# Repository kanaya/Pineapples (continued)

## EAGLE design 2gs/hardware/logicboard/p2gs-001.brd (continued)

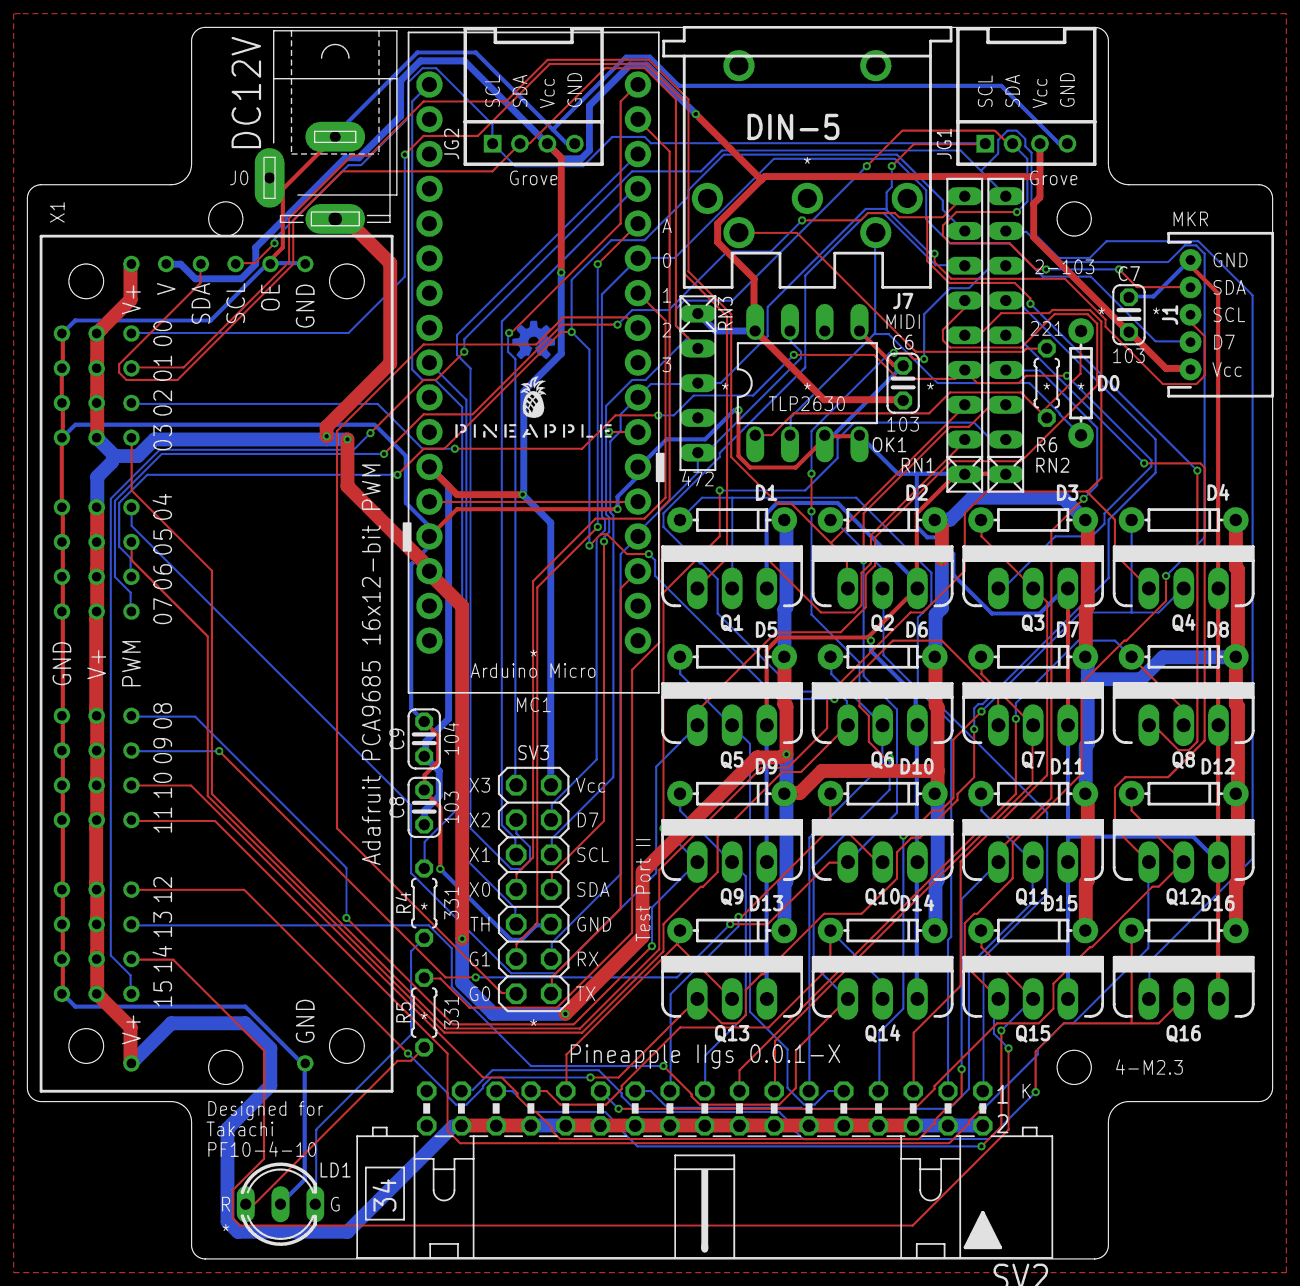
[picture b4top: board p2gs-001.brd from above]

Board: 2 copper layers, 91.0 x 90.0 mm, 56 parts (1 on the bottom side), 55 nets.

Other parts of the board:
JG2: Grove/2; 4P-2.0-90D

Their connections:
GND: JG2.4; also elsewhere on the board
SCL: JG2.1; also elsewhere on the board
SDA: JG2.2; also elsewhere on the board
VCC: JG2.3; also elsewhere on the board

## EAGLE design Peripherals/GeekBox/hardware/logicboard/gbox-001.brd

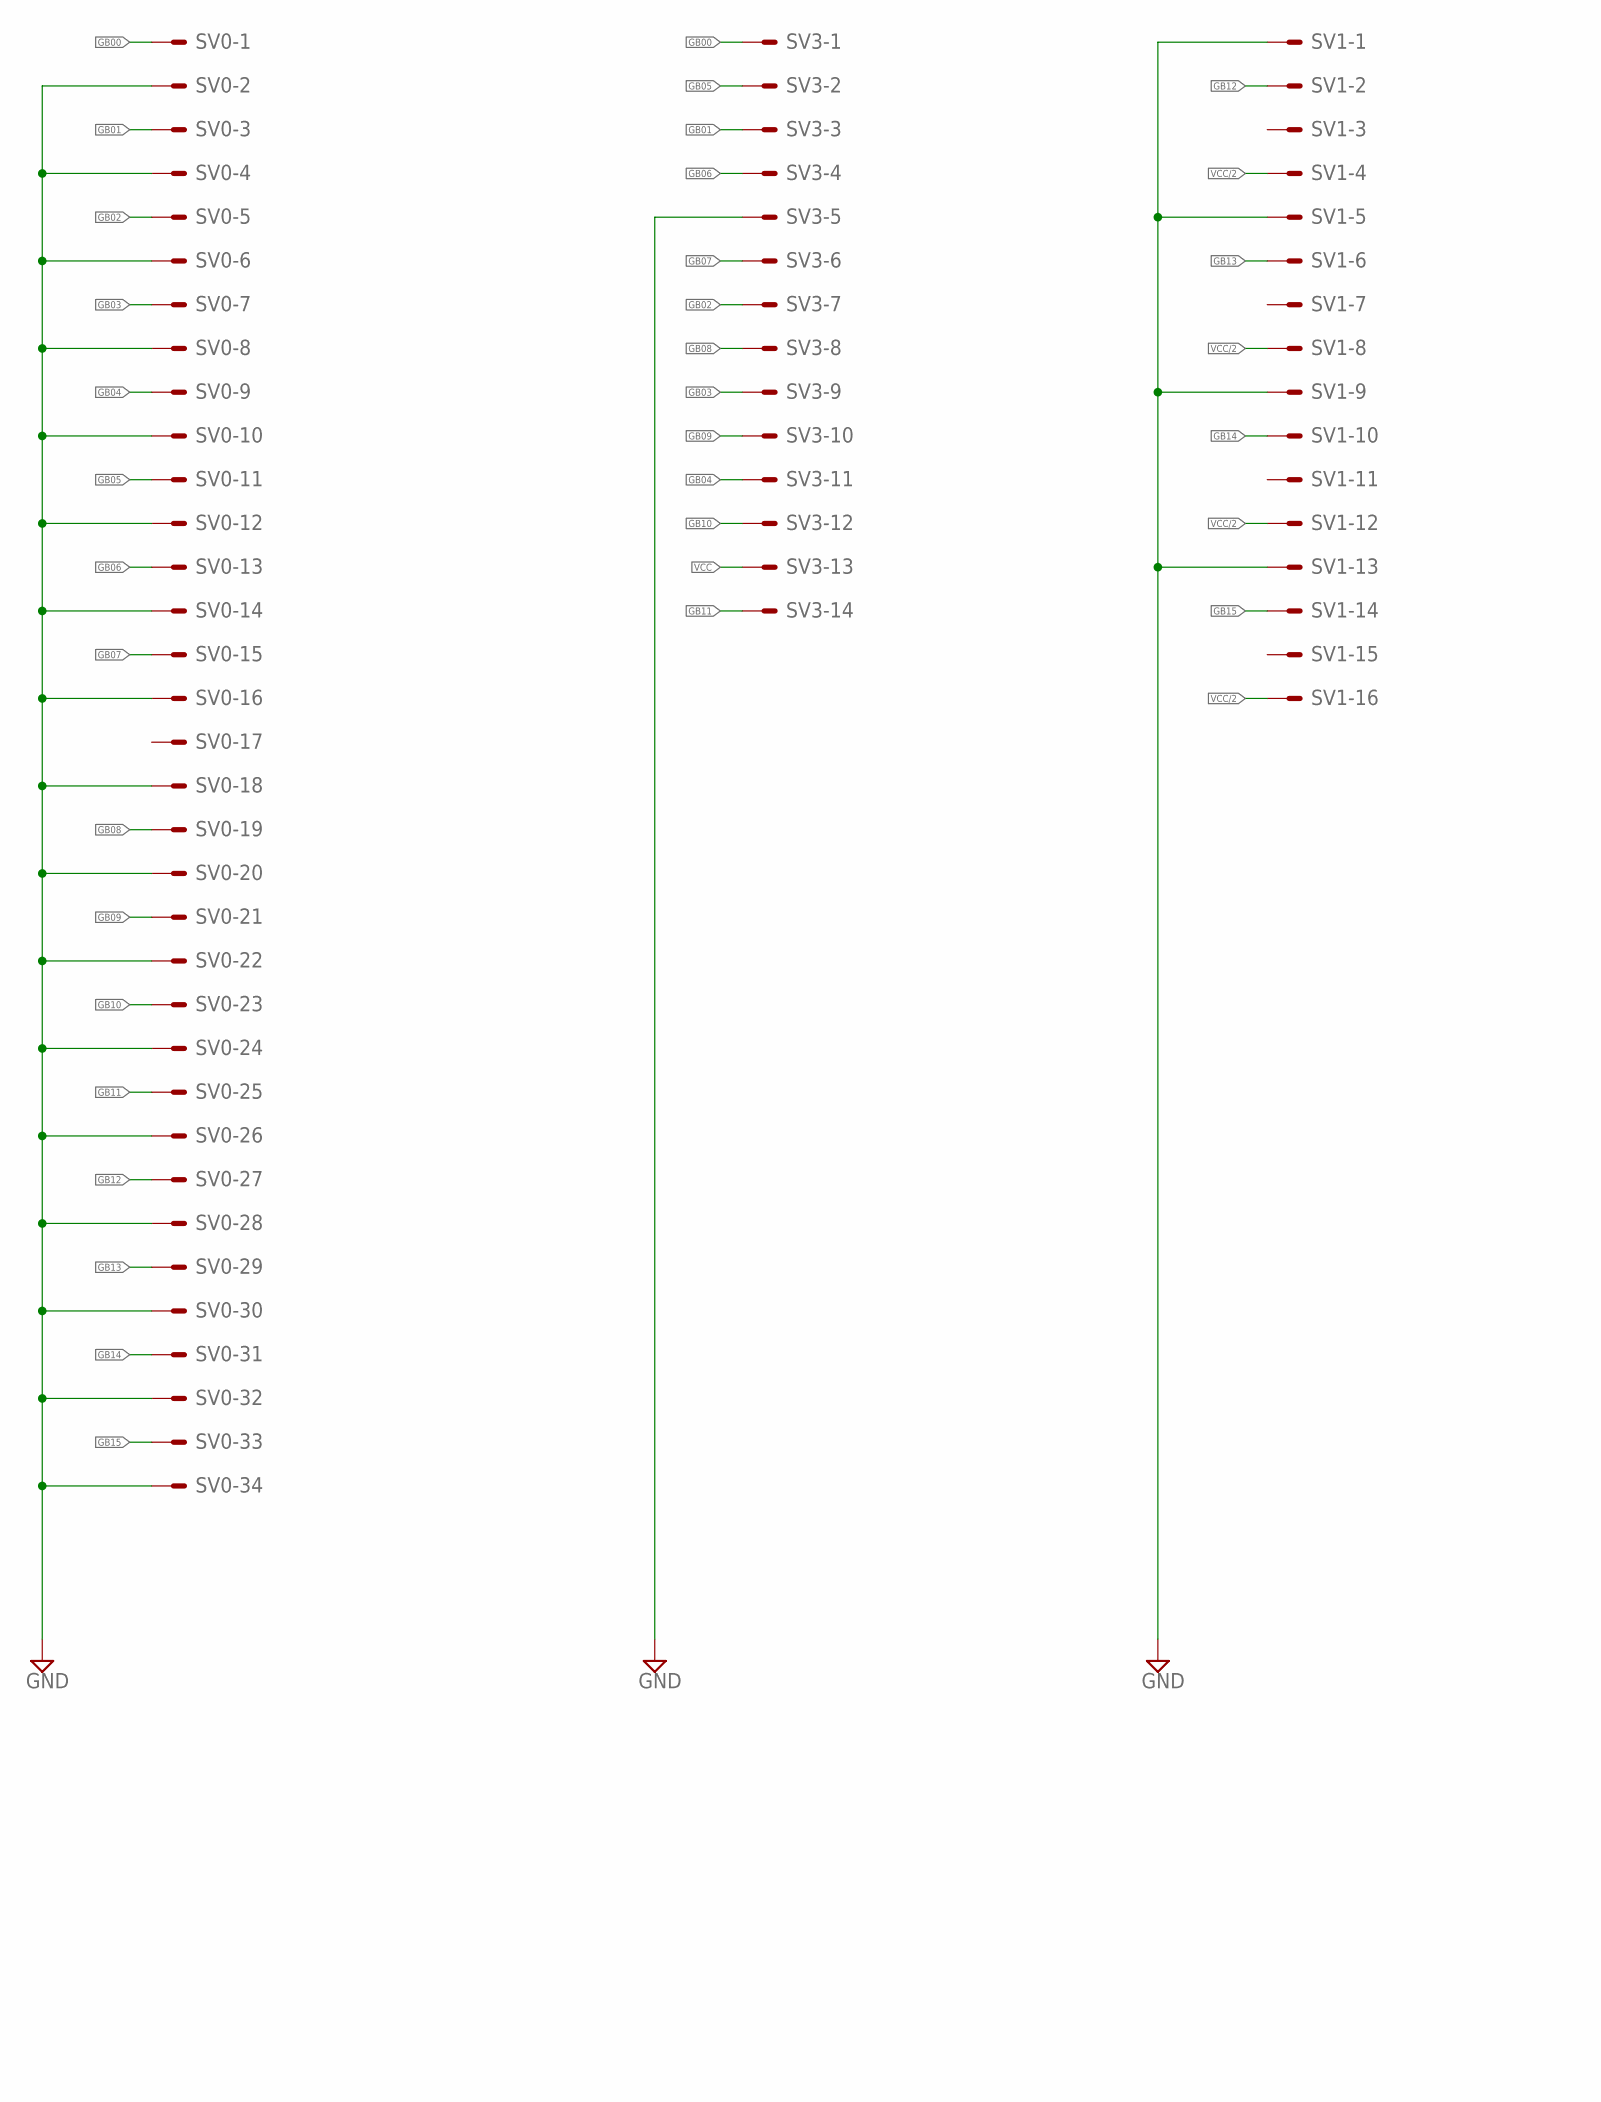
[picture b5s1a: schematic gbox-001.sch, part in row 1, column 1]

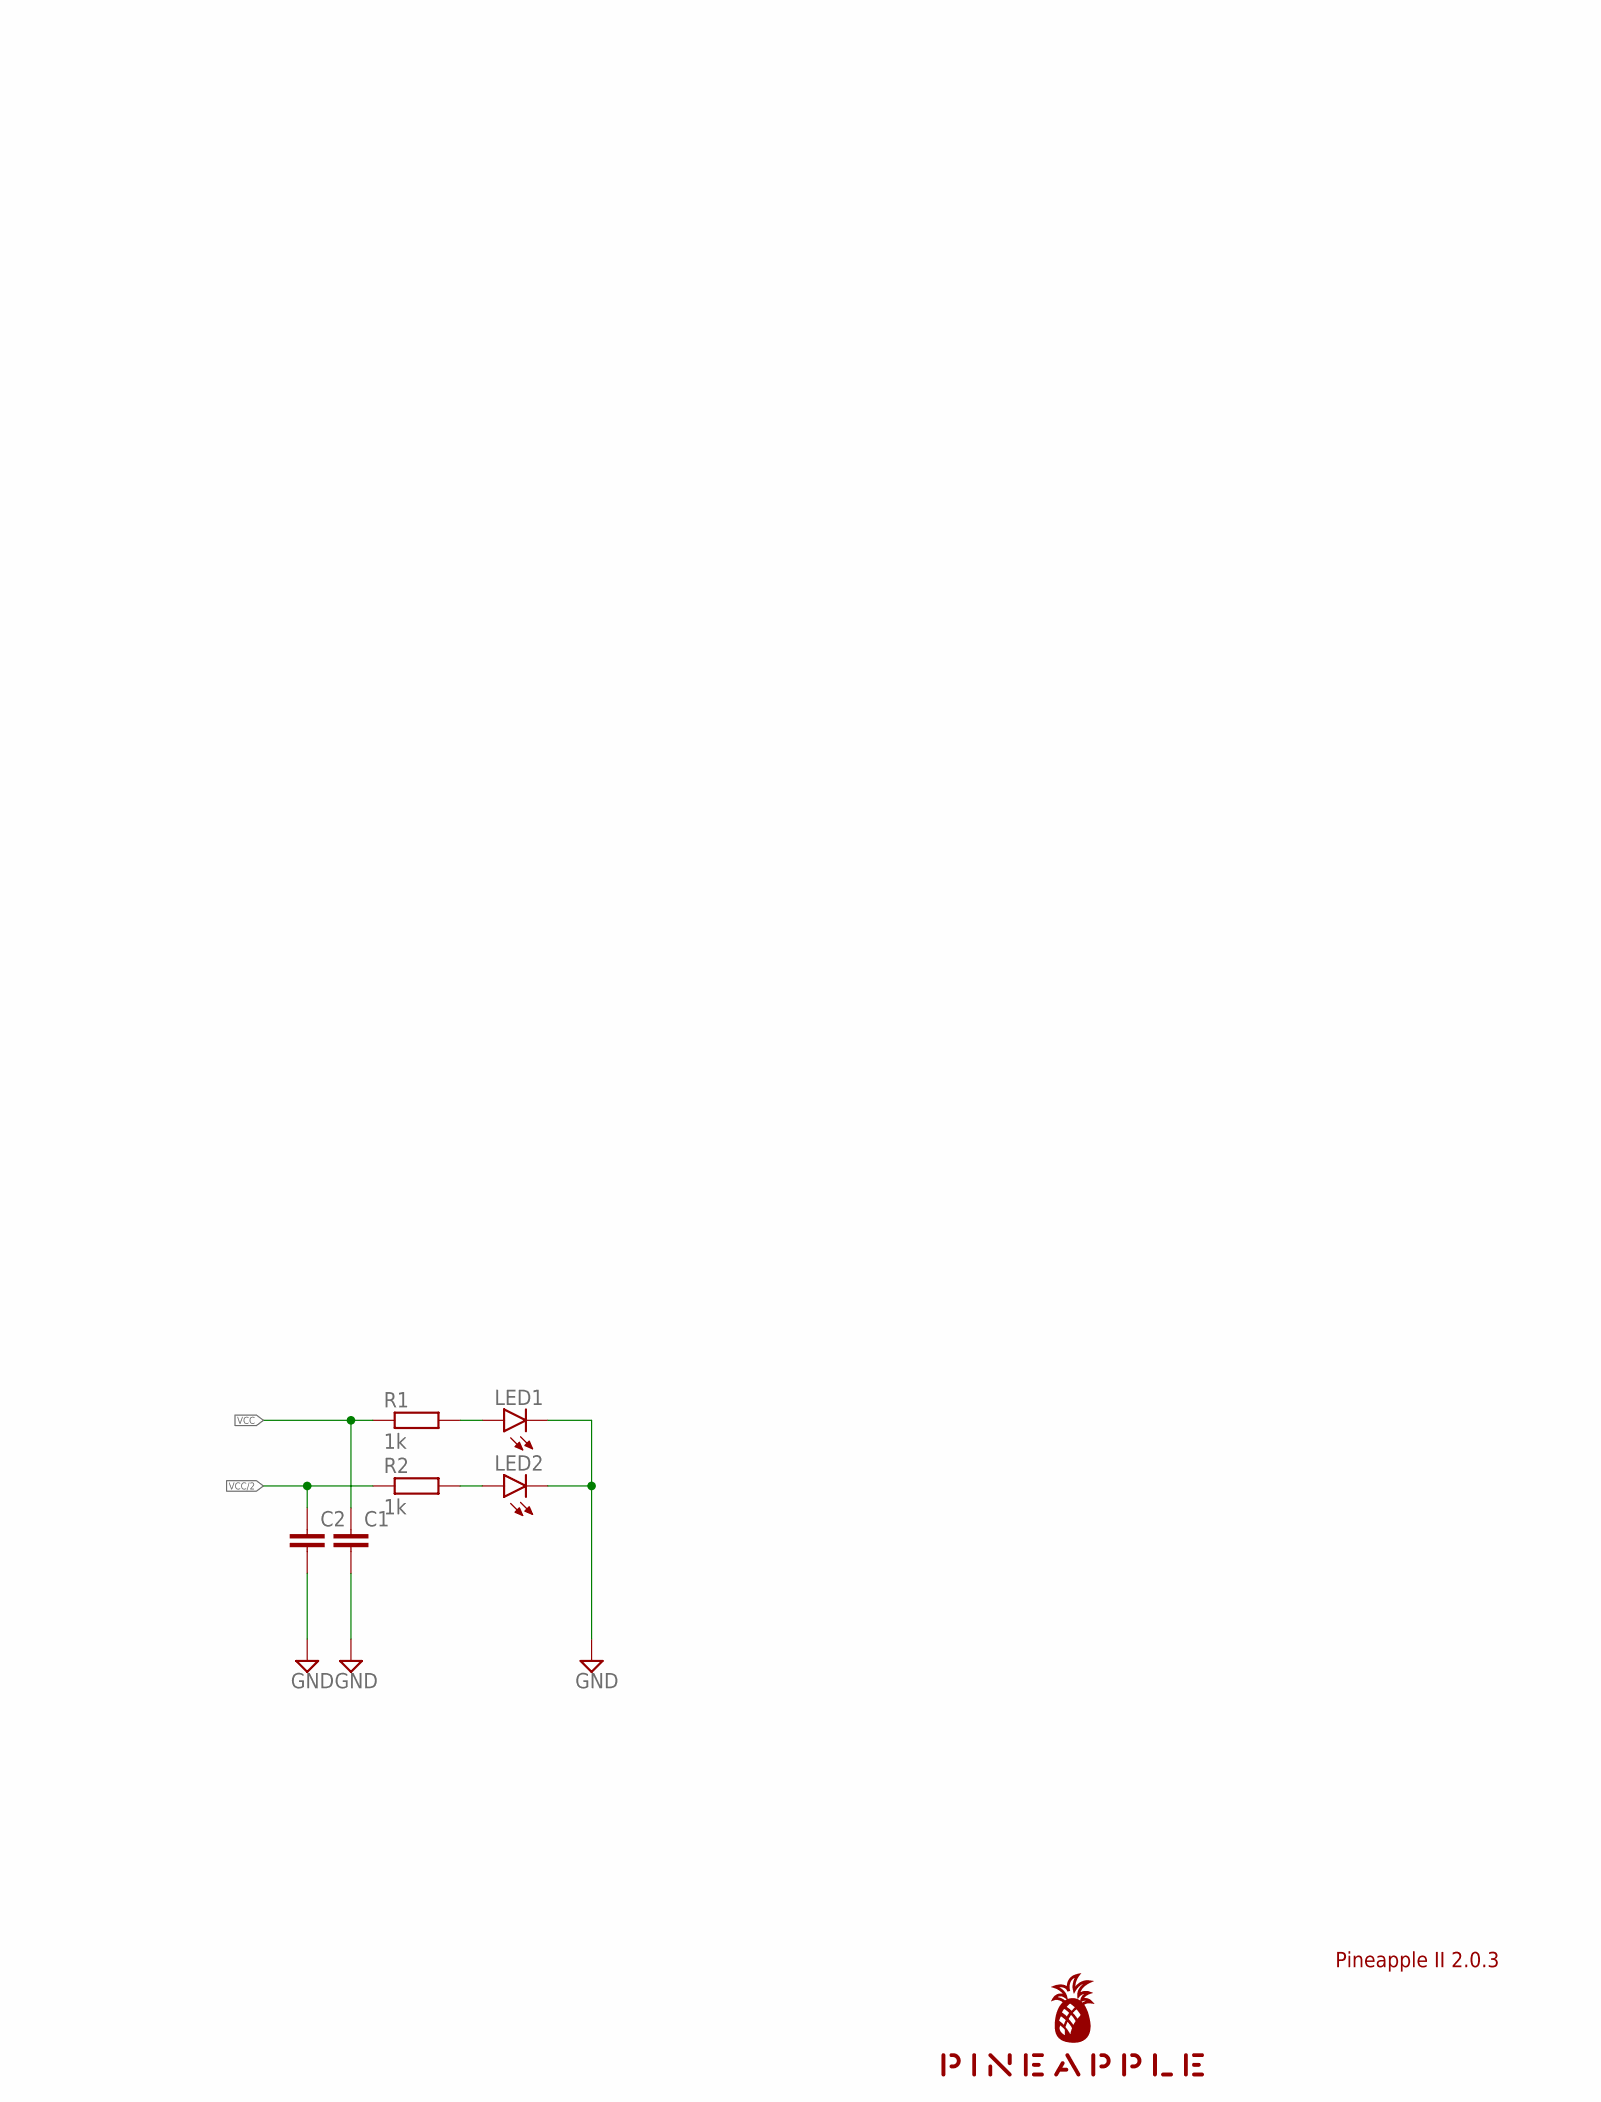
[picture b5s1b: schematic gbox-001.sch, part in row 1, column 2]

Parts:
C1, C2: C-EU025-025X050; C025-025X050
LED1, LED2: LED3MM
R1, R2: 1k; 0204/5
SV0: ML34LE; ML34L
SV1: ML16LE; ML16L
SV3: ML14LE; ML14L
U$1: PINEAPPLE450_SILK

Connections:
GB00: SV0.1, SV3.1
GB01: SV0.3, SV3.3
GB02: SV0.5, SV3.7
GB03: SV0.7, SV3.9
GB04: SV0.9, SV3.11
GB05: SV0.11, SV3.2
GB06: SV0.13, SV3.4
GB07: SV0.15, SV3.6
GB08: SV0.19, SV3.8
GB09: SV0.21, SV3.10
GB10: SV0.23, SV3.12
GB11: SV0.25, SV3.14
GB12: SV0.27, SV1.2
GB13: SV0.29, SV1.6
GB14: SV0.31, SV1.10
GB15: SV0.33, SV1.14
GND: C1.2, C2.2, LED1.K (C), LED2.K (C), SV0.2, SV0.4, SV0.6, SV0.8, SV0.10, SV0.12, SV0.14, SV0.16, SV0.18, SV0.20, SV0.22, SV0.24, SV0.26, SV0.28, SV0.30, SV0.32, SV0.34, SV1.1, SV1.5, SV1.9, SV1.13, SV3.5
VCC: C1.1, R1.1, SV3.13
VCC2LED: LED2.A, R2.2
VCC/2: C2.1, R2.1, SV1.4, SV1.8, SV1.12, SV1.16
VCCLED: LED1.A, R1.2

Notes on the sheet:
Pineapple II 2.0.3

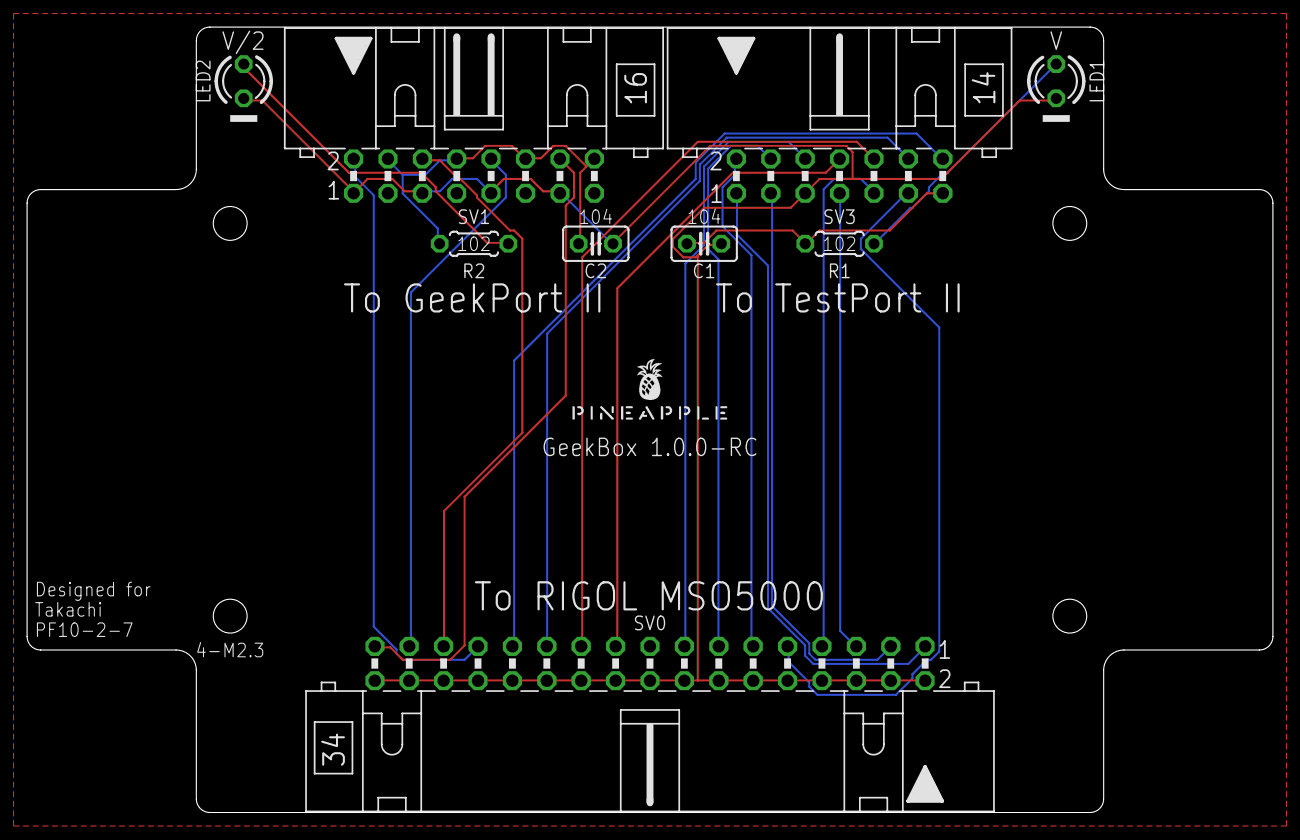
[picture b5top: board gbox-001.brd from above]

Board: 2 copper layers, 92.0 x 58.0 mm, 10 parts (0 on the bottom side), 21 nets.

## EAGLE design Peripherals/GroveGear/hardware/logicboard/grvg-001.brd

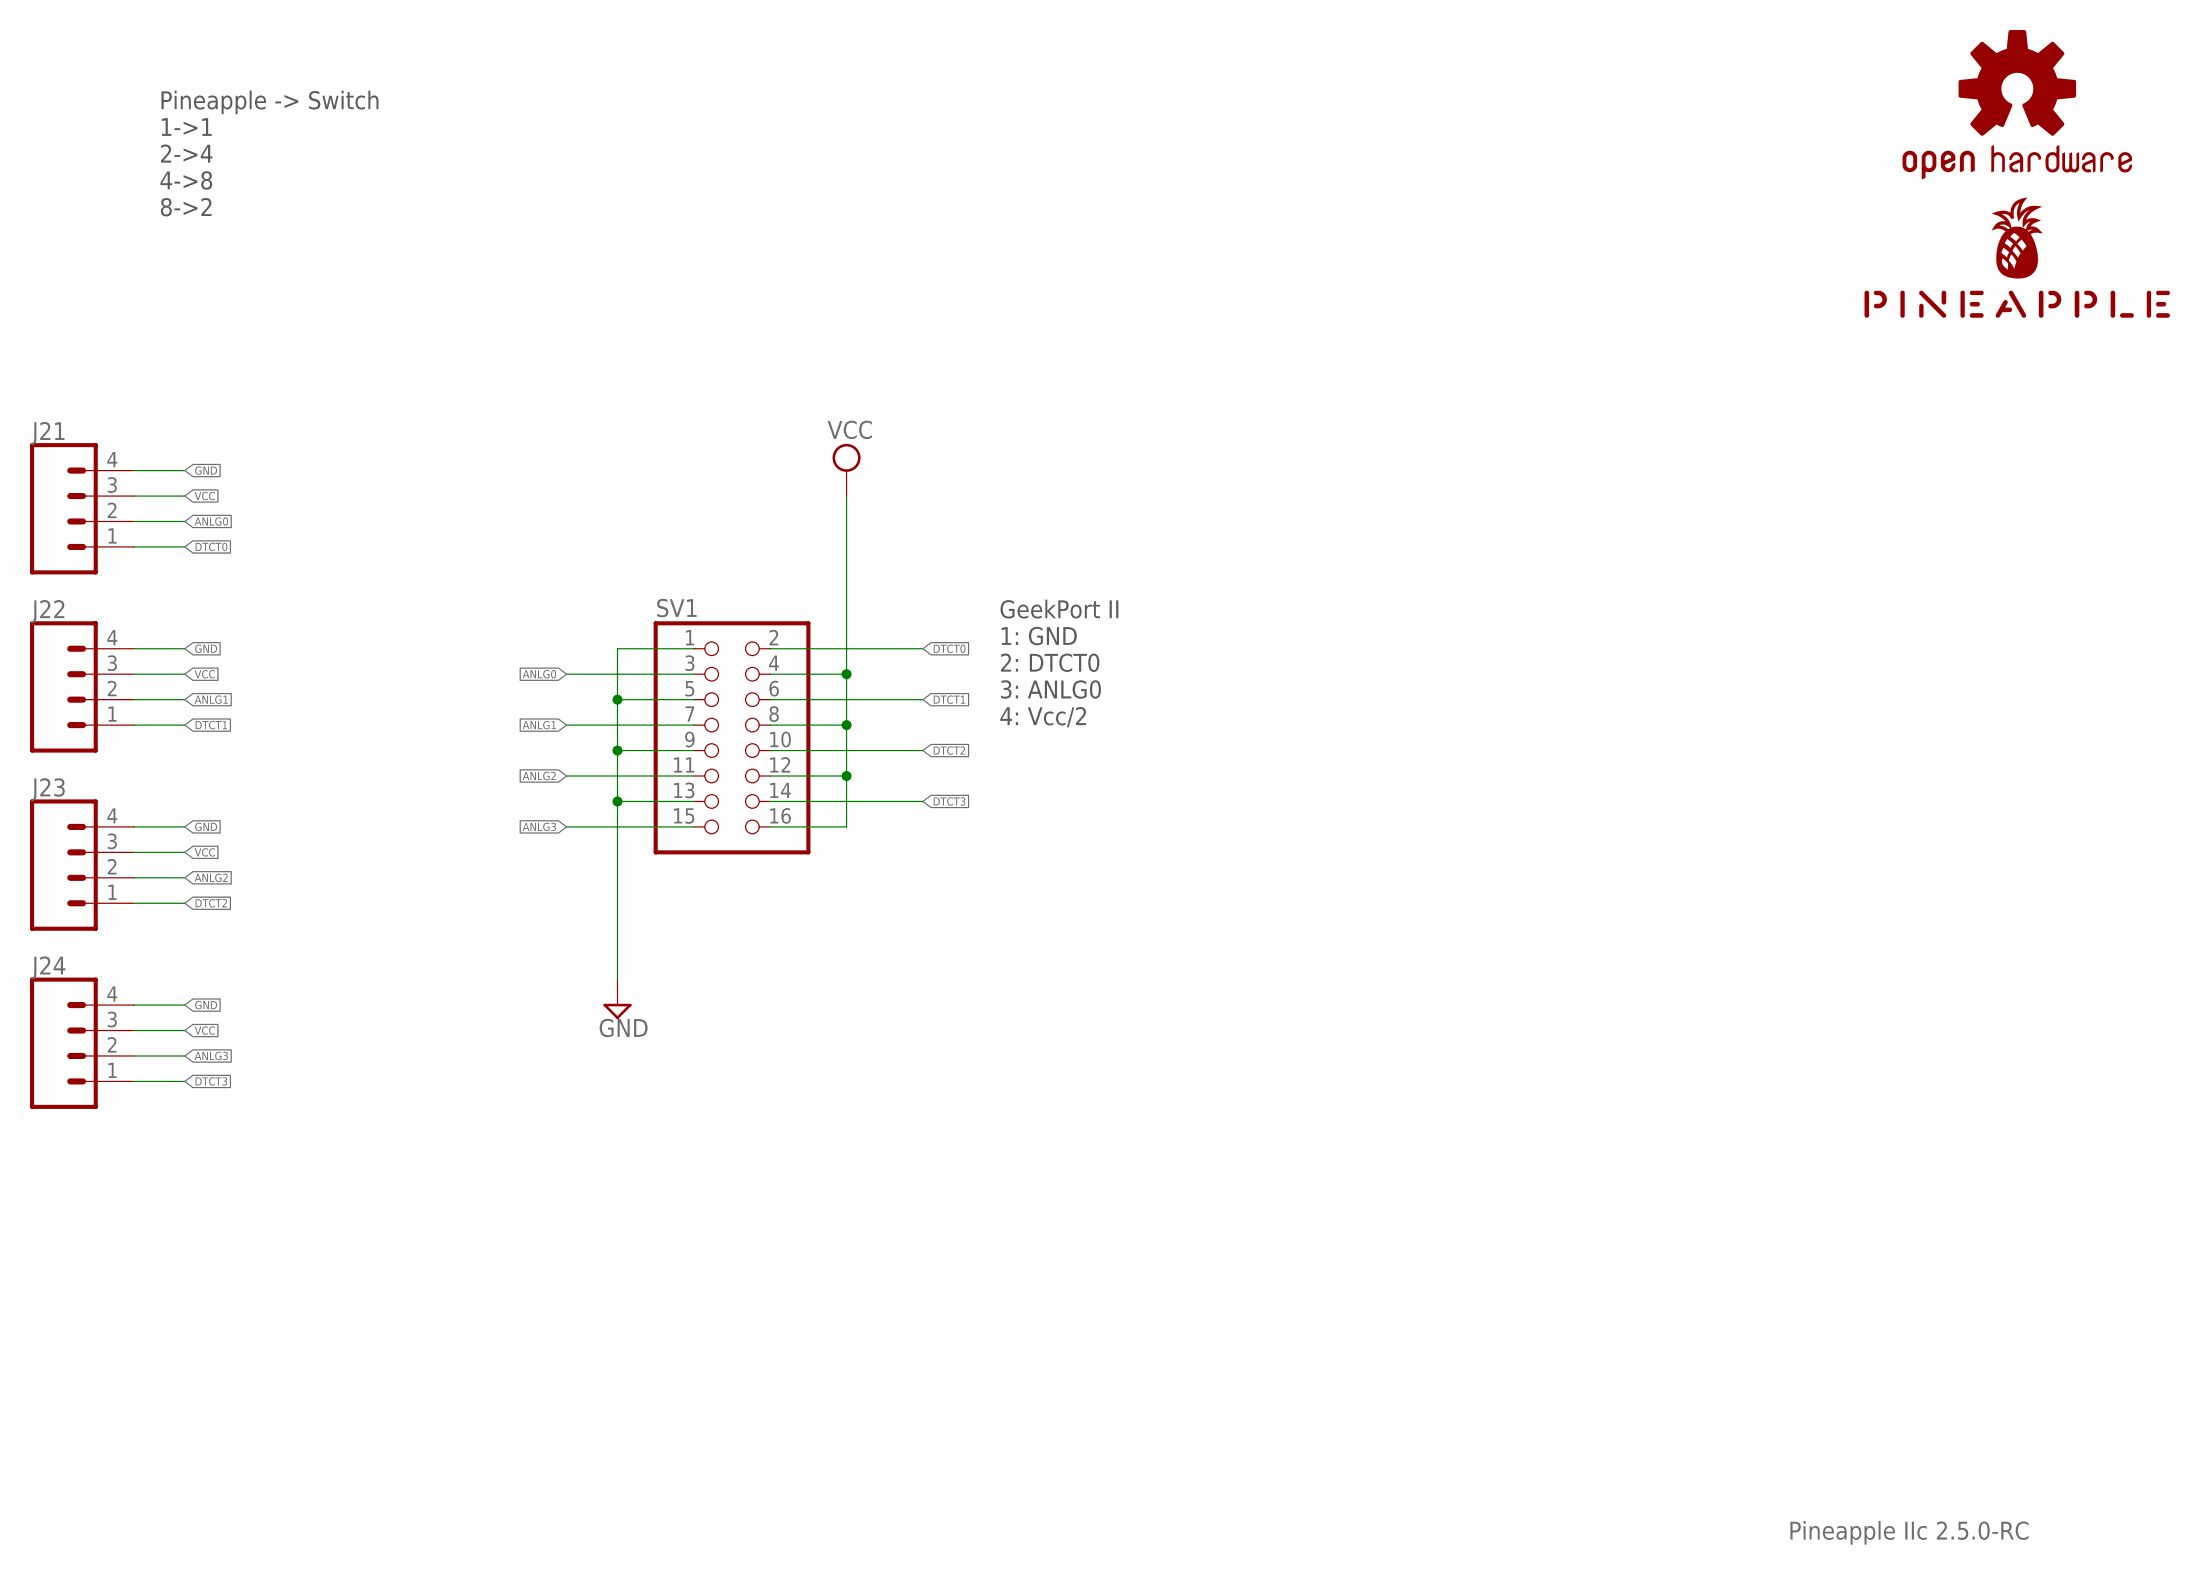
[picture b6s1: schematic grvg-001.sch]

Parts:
J21, J22, J23, J24: CONN_04JST-PTH-VERT; JST-4-PTH-VERT
LOGO1: OSHW-LOGOS-COPPER; OSHW-LOGO-S_COPPER
SV1: PINHD-2X8; 2X08
U$1: PINEAPPLE450_SILK

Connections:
ANLG0: J21.2, SV1.3
ANLG1: J22.2, SV1.7
ANLG2: J23.2, SV1.11
ANLG3: J24.2, SV1.15
DTCT0: J21.1, SV1.2
DTCT1: J22.1, SV1.6
DTCT2: J23.1, SV1.10
DTCT3: J24.1, SV1.14
GND: J21.4, J22.4, J23.4, J24.4, SV1.1, SV1.5, SV1.9, SV1.13
VCC: J21.3, J22.3, J23.3, J24.3, SV1.4, SV1.8, SV1.12, SV1.16

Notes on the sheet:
Pineapple IIc 2.5.0-RC
Pineapple -> Switch 1->1 2->4 4->8 8->2
GeekPort II 1: GND 2: DTCT0 3: ANLG0 4: Vcc/2

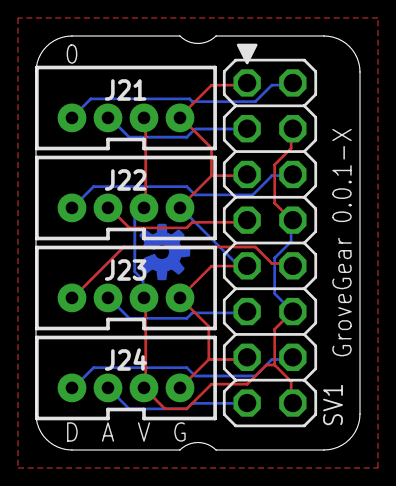
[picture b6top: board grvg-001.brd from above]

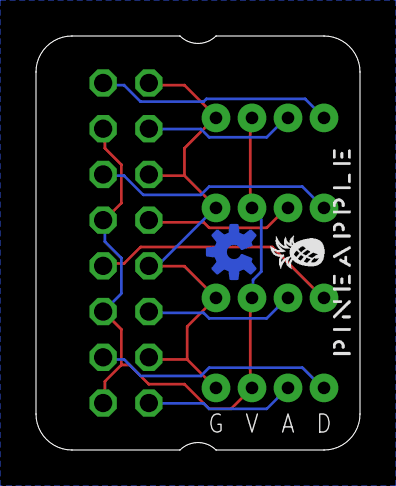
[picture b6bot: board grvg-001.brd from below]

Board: 2 copper layers, 18.0 x 23.0 mm, 7 parts (2 on the bottom side), 10 nets.

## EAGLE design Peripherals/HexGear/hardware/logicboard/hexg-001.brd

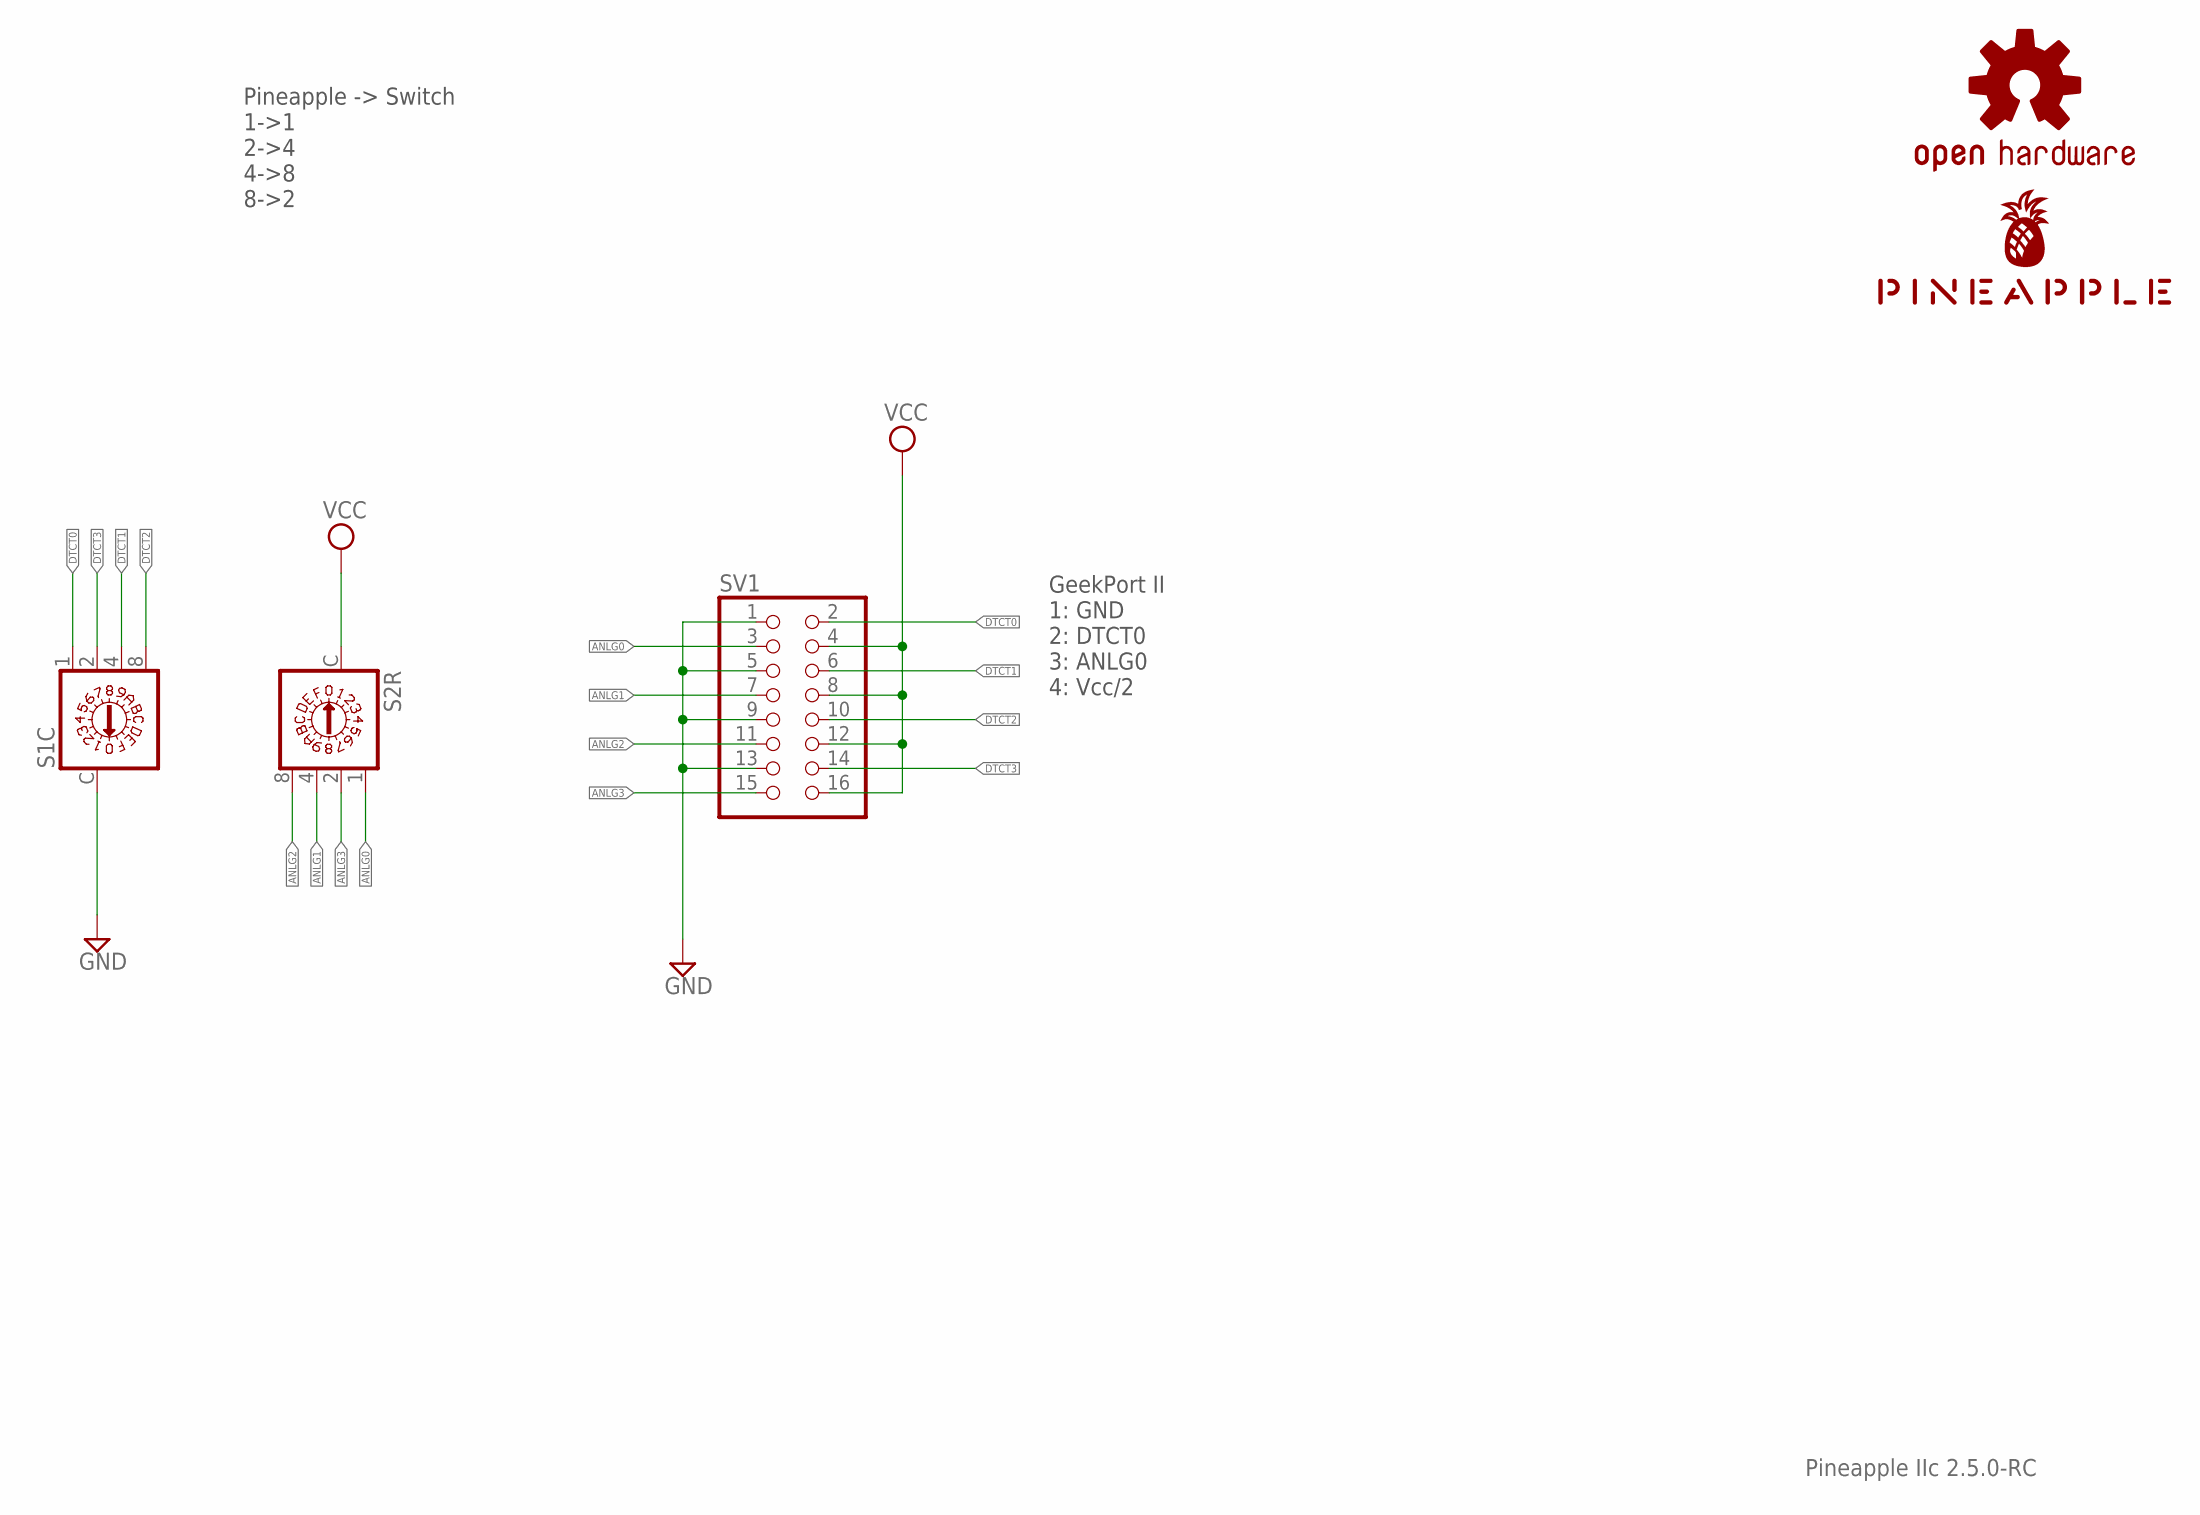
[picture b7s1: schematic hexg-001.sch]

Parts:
LOGO1: OSHW-LOGOS-COPPER; OSHW-LOGO-S_COPPER
S1C, S2R: A1353HEX
SV1: PINHD-2X8; 2X08
U$1: PINEAPPLE450_SILK

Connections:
ANLG0: S2R.1, SV1.3
ANLG1: S2R.4, SV1.7
ANLG2: S2R.8, SV1.11
ANLG3: S2R.2, SV1.15
DTCT0: S1C.1, SV1.2
DTCT1: S1C.4, SV1.6
DTCT2: S1C.8, SV1.10
DTCT3: S1C.2, SV1.14
GND: S1C.C, SV1.1, SV1.5, SV1.9, SV1.13
VCC: S2R.C, SV1.4, SV1.8, SV1.12, SV1.16

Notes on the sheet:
Pineapple IIc 2.5.0-RC
Pineapple -> Switch 1->1 2->4 4->8 8->2
GeekPort II 1: GND 2: DTCT0 3: ANLG0 4: Vcc/2

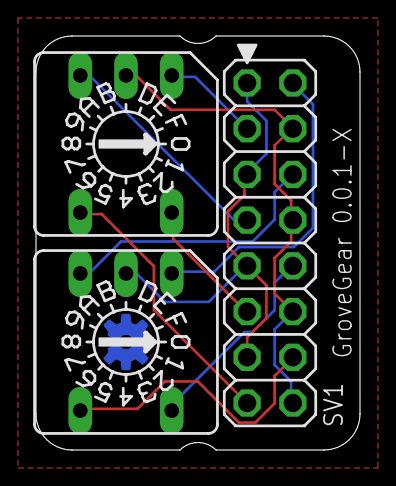
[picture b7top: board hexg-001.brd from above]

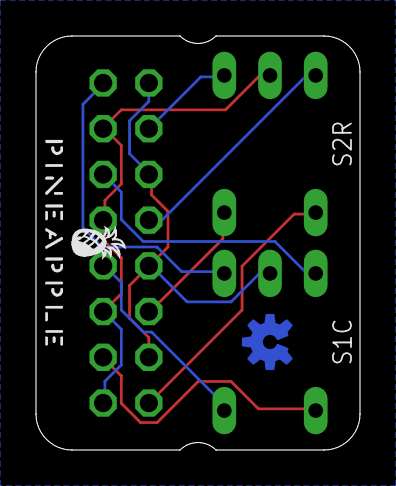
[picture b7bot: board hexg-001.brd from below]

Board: 2 copper layers, 18.0 x 23.0 mm, 5 parts (2 on the bottom side), 10 nets.
